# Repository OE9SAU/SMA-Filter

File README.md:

**Filter-PCB with SMA connectors to place SMD 0805 filter chips from Johanson Technology**

SMD0805, 373MHz Mittenfrequenz, Johanson Technology, 0400LP15A0122001E

Housing: 

2x copper hose cap
https://www.obi.at/loetfittings/kappe-fuer-loetfittings-12-mm-kupfer/p/6531586

1x copper hose ⌀10mm

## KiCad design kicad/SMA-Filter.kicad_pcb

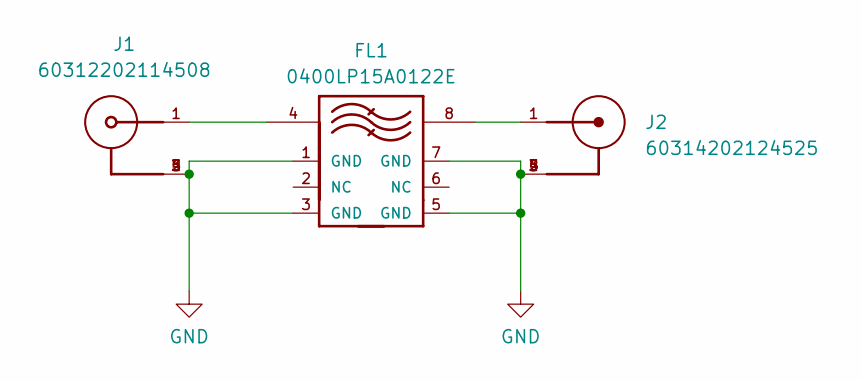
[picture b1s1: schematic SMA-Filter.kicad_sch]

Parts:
FL1: 0400LP15A0122E; FIL_0400LP15A0122E; PARTREV 1.1
J1: 60312202114508
J2: 60314202124525

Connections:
GND: FL1.1 (GND), FL1.3 (GND), FL1.5 (GND), FL1.7 (GND), J1.2, J1.3, J1.4, J1.5, J2.2, J2.3, J2.4, J2.5
unnamed: FL1.4, J1.1
unnamed: FL1.8, J2.1

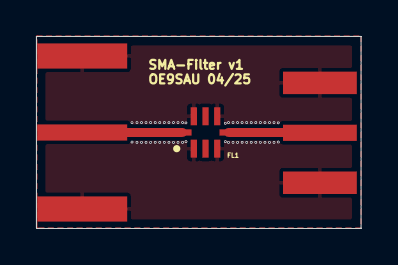
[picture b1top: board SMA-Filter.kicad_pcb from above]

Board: 2 copper layers, 18.0 x 10.7 mm, 3 parts (0 on the bottom side), 3 nets.

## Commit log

2025-04-24 Update Git
2025-04-24 Update Files
2025-06-10 PCB Update
2025-06-10 Via Update
2025-06-10 PCB pic
2025-06-30 nanovna
2025-07-06 Pic Update
2025-07-06 Pic Uopdate
2025-07-06 Pic Upload
